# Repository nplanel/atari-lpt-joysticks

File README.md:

# Atari LPT/parallel port joysticks extension
## printer port 4 Players adaptor

4 Player games:

* Frogs https://www.hd-videofilm.com/frogs/
* Gauntlet II
* Leathernecks
* ST Soccer
* ... ?

## Pinout

|  DB 25   |  Joystick 3   |  Joystick 4 |
|----------|:-------------:|------------:|
|    1     |     | 6 |
|    2     |     | 1 |
|    3     |     | 2 |
|    4     |     | 3 |
|    5     |     | 4 |
|    6     |  1  |   |
|    7     |  2  |   |
|    8     |  3  |   |
|    9     |  4  |   |
|    11    |  6  |   |
|    24  (GND)   | 8 |   |
|    25  (GND)   |   | 8 |

## Software

C library and GFA binding are available here : https://github.com/bganne/libjoy.git

### made @ ADN 2022 https://demozoo.org/parties/4452/

# Have fun /I\\ :)

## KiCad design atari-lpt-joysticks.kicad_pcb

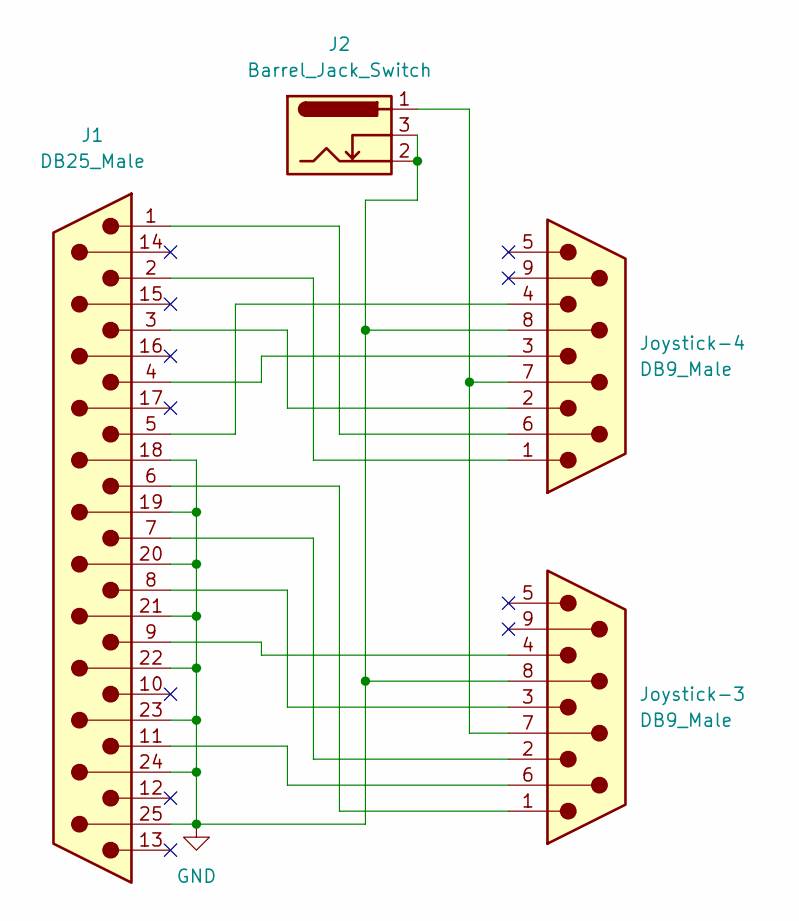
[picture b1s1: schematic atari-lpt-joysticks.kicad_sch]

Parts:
J1: DB25_Male; DSUB-25_Male_EdgeMount_P2.77mm
J2: Barrel_Jack_Switch; BarrelJack_GCT_DCJ200-10-A_Horizontal
Joystick-3, Joystick-4: DB9_Male; DSUB-9_Male_EdgeMount_P2.77mm

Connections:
GND: J1.18, J1.19, J1.20, J1.21, J1.22, J1.23, J1.24, J1.25, J2.2, J2.3, Joystick-3.8, Joystick-4.8
unnamed: J1.1, Joystick-4.6
unnamed: J1.2, Joystick-4.1
unnamed: J1.3, Joystick-4.2
unnamed: J1.4, Joystick-4.3
unnamed: J1.5, Joystick-4.4
unnamed: J1.6, Joystick-3.1
unnamed: J1.7, Joystick-3.2
unnamed: J1.8, Joystick-3.3
unnamed: J1.9, Joystick-3.4
unnamed: J1.11, Joystick-3.6
unnamed: J2.1, Joystick-3.7, Joystick-4.7

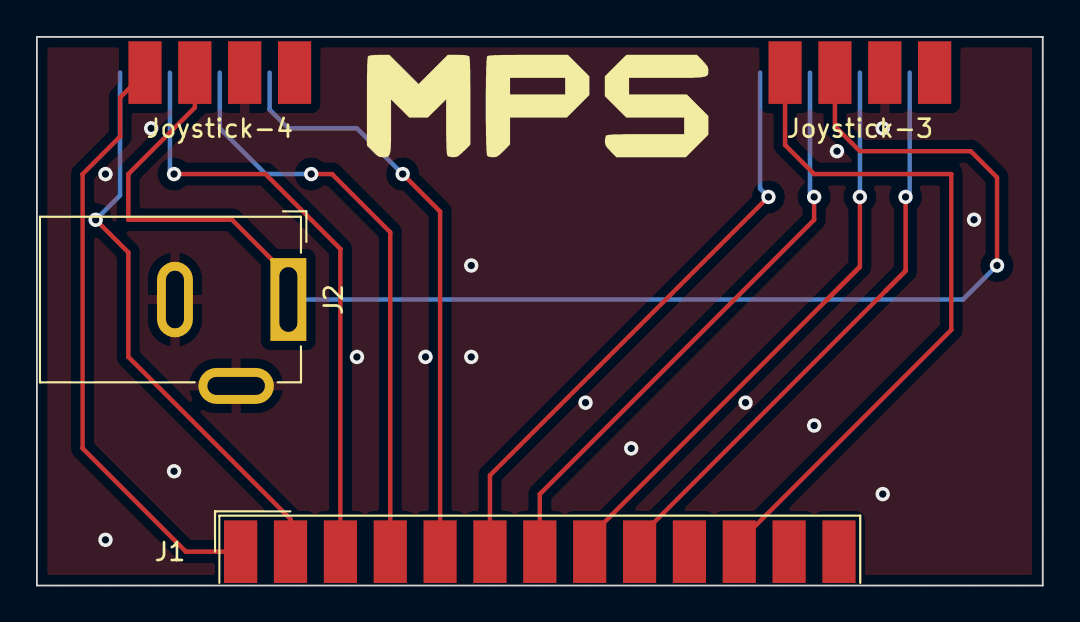
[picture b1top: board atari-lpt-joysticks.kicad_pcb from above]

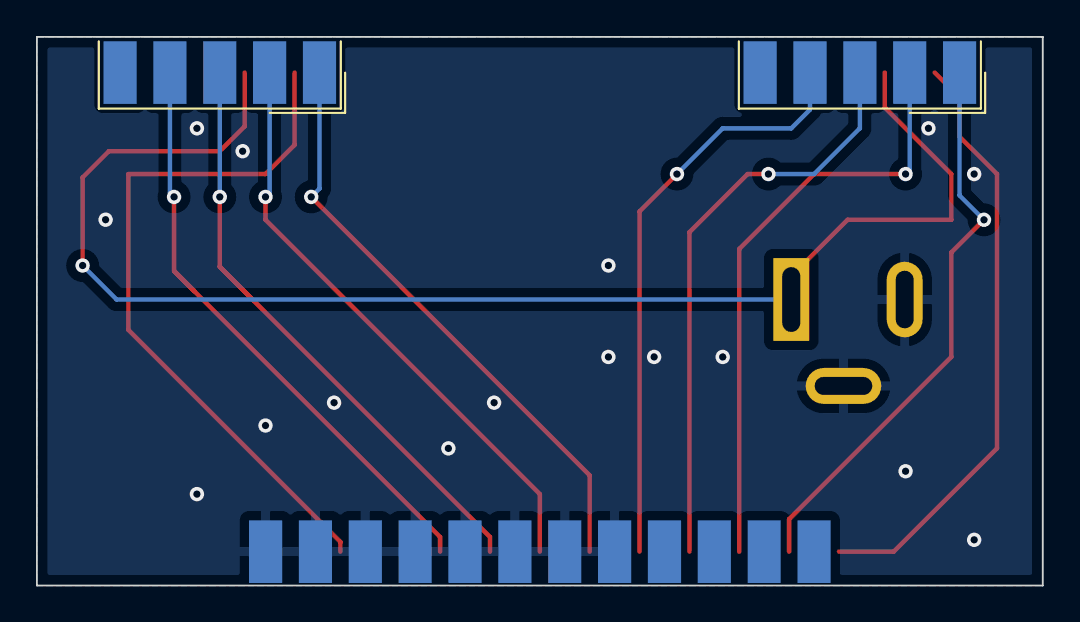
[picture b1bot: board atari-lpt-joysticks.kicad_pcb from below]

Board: 2 copper layers, 55.9 x 30.5 mm, 4 parts (2 on the bottom side), 12 nets.

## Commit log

2022-08-01 Atari ST LPT/parallel port joysticks extension
2022-08-01 Create README.md
    Readme games list and libjoy library
2022-08-01 Add ADN 2022 reference
2022-08-01 Add adapter PCB pic
2022-08-10 swap joystick 3 and 4
    hardware description are not correct :
    * http://atari4ever.free.fr/hardware/zip/4joy_ada.zip
    * https://www.atari-forum.com/viewtopic.php?p=318615#p318615
    Gauntlet 2 and Leatherneck game use this pinout
    Discussion : https://github.com/hatari/hatari/pull/22
